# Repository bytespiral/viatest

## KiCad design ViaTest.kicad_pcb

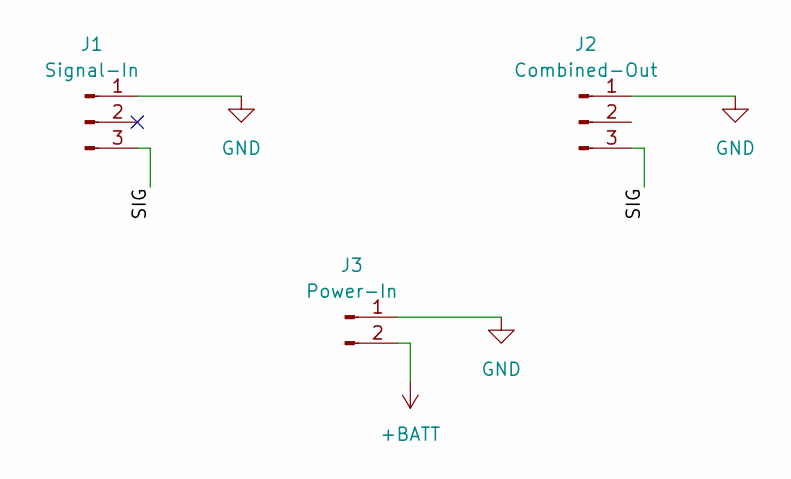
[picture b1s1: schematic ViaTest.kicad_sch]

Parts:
J1: Signal-In; TerminalBlock_Phoenix_PTSM-0,5-3-2,5-V-SMD_1x03-1MP_P2.50mm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
J2: Combined-Out; TerminalBlock_Phoenix_PTSM-0,5-3-2,5-V-SMD_1x03-1MP_P2.50mm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
J3: Power-In; TerminalBlock_Phoenix_PTSM-0,5-2-2,5-V-SMD_1x02-1MP_P2.50mm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

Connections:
+BATT: J2.2, J3.2
/SIG: J1.3, J2.3
GND: J1.1, J2.1, J3.1

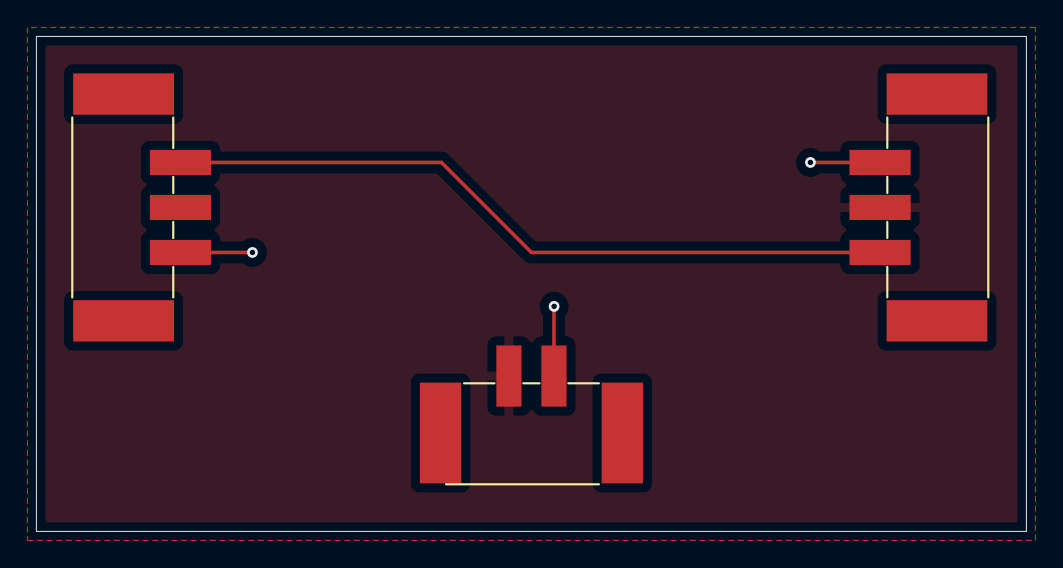
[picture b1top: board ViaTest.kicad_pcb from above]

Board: 2 copper layers, 55.0 x 27.5 mm, 3 parts (0 on the bottom side), 3 nets.

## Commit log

2025-01-27 JLCPCB package
